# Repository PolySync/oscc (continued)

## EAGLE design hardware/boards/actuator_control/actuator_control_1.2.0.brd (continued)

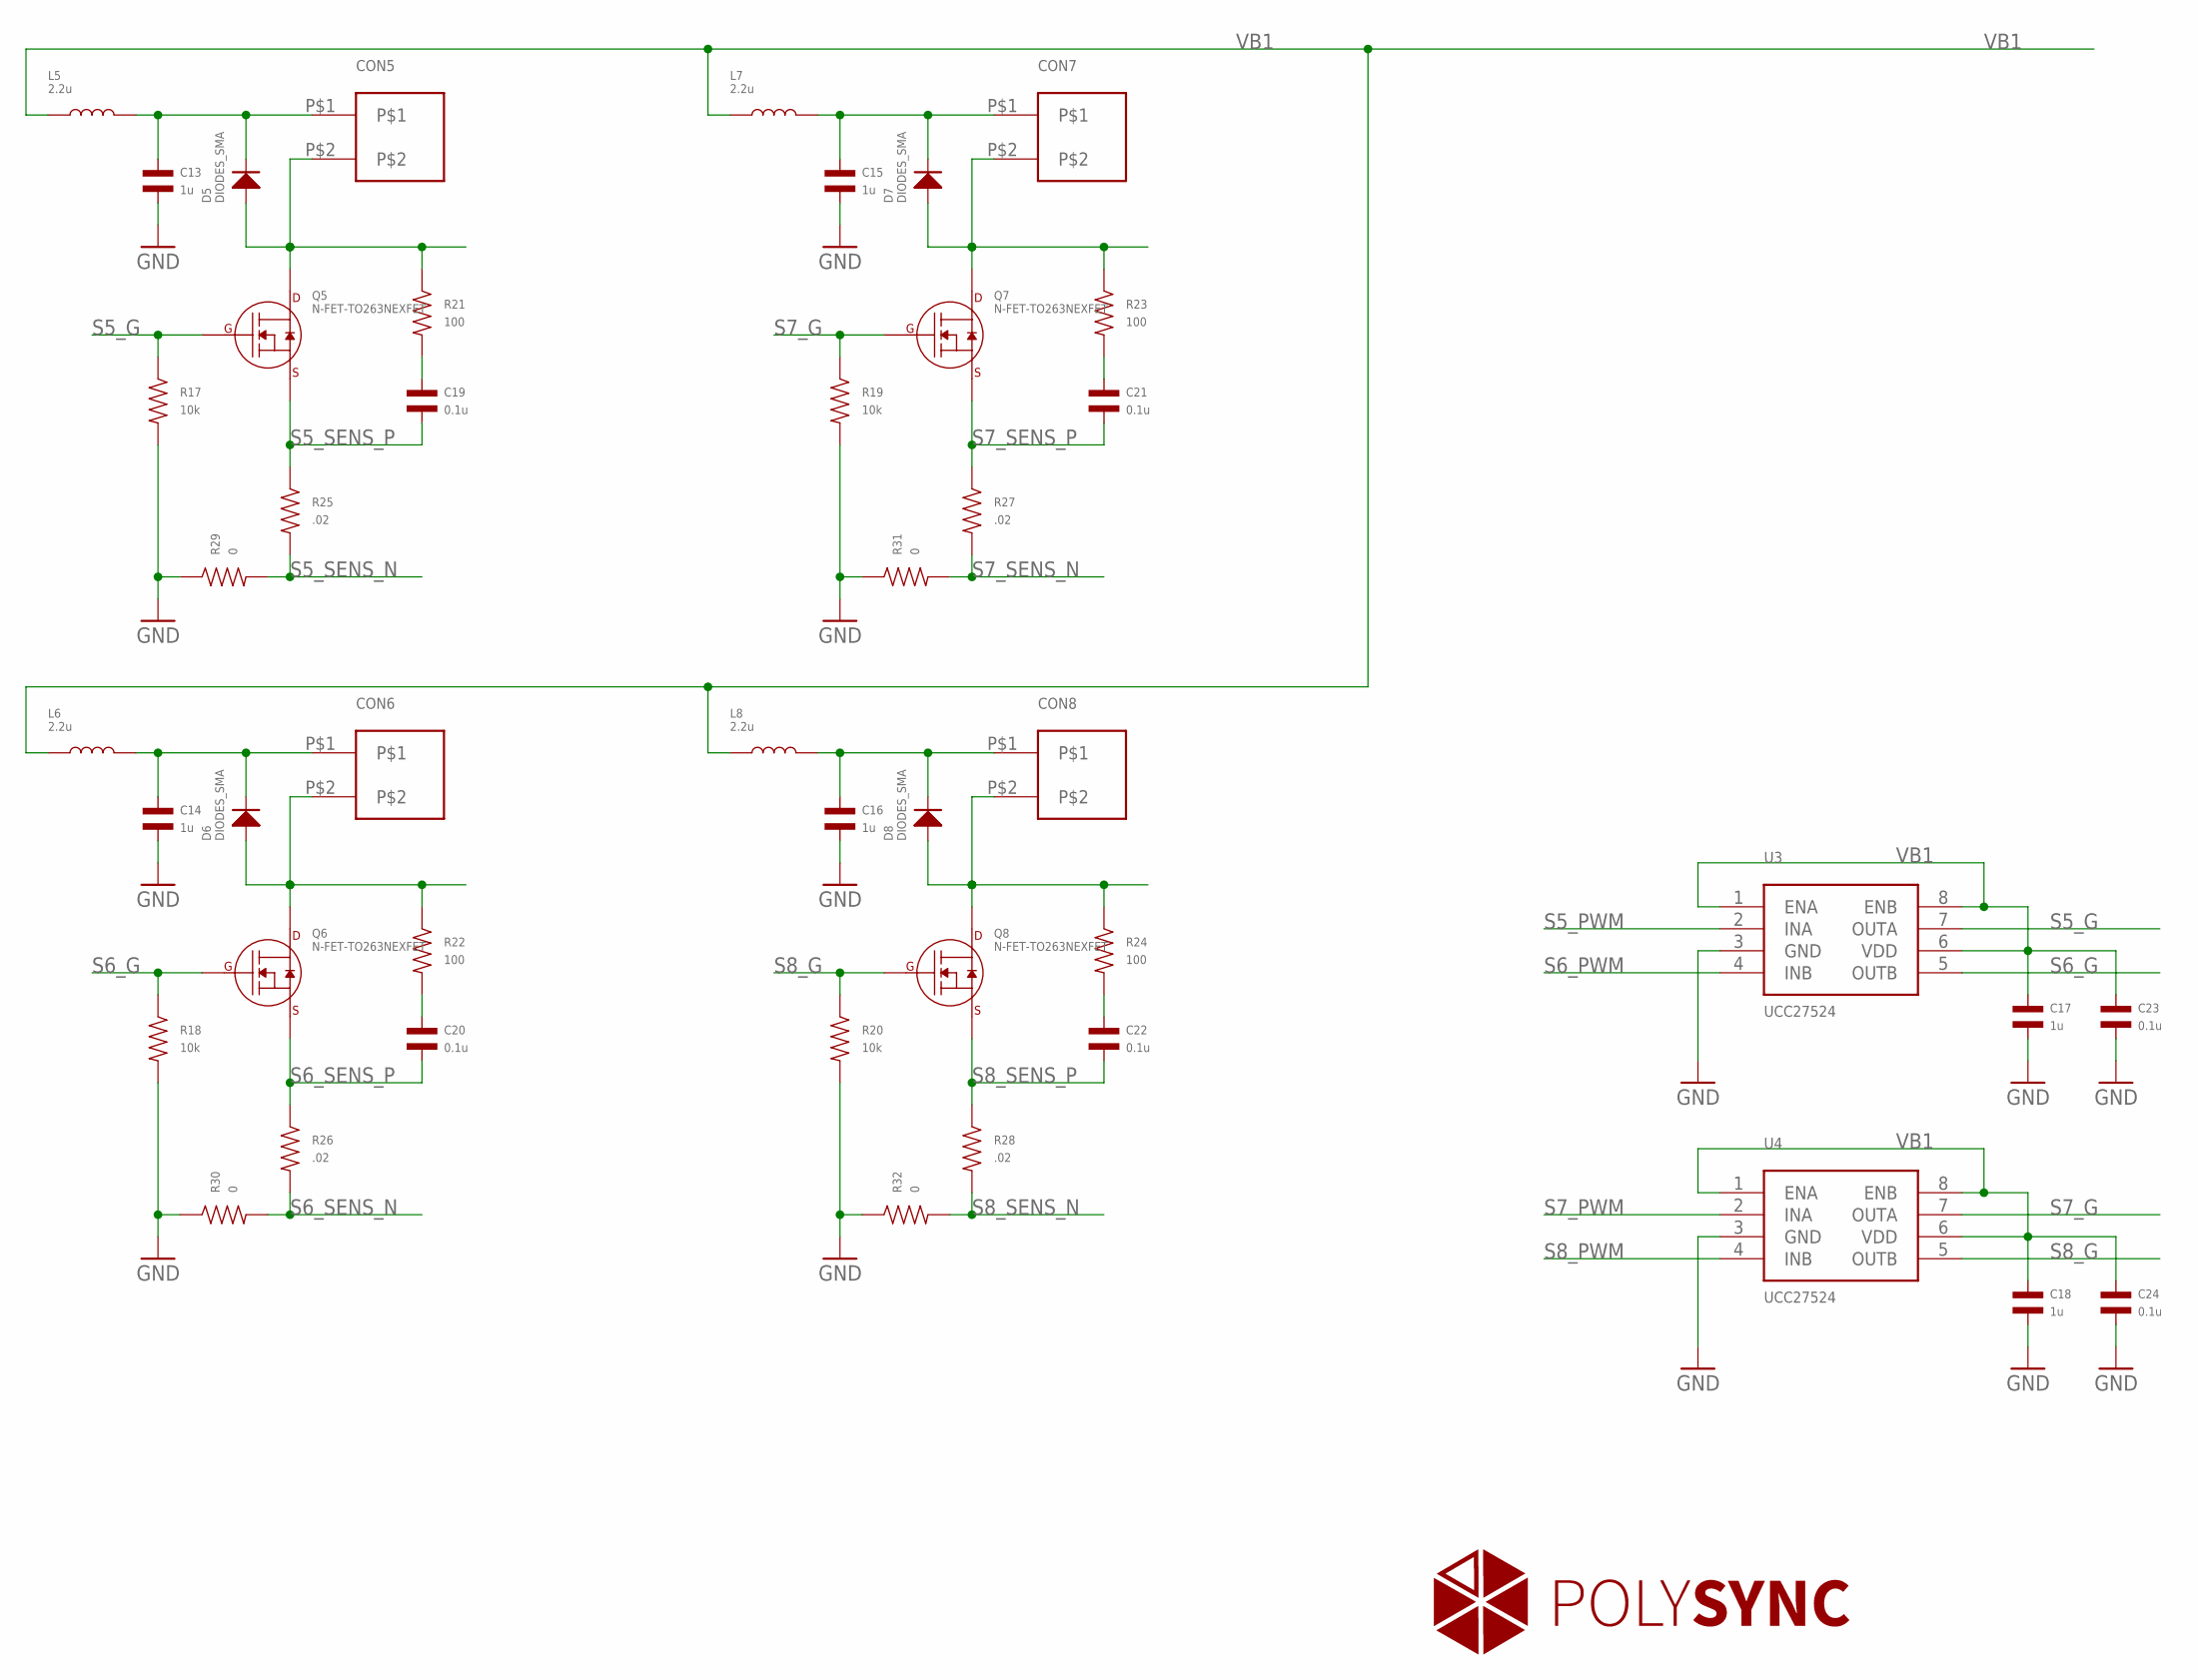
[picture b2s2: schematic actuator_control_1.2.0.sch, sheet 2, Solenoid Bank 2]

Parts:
C13, C14, C15, C16, C17, C18: 1u; C1206
C19, C20, C21, C22, C23, C24: 0.1u; C0805
CON5, CON6, CON7, CON8: CON23.5MM; PHOENIX_2_45
D5, D6, D7, D8: DIODES_SMA; SMA
L5, L6, L7, L8: 2.2u; SRP7050; PARTNO SRP7050TA-2R2M
Q5, Q6, Q7, Q8: N-FET-TO263NEXFET; SON8-DQJ
R17, R18, R19, R20: 10k; R0402
R21, R22, R23, R24: 100; R0805
R25, R26, R27, R28: .02; R1206
R29, R30, R31, R32: 0; R0805
U3, U4: UCC27524; SOIC-8

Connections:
GND: C13.P$2, C14.P$2, C15.P$2, C16.P$2, C17.P$2, C18.P$2, C23.P$2, C24.P$2, R17.P$2, R18.P$2, R19.P$2, R20.P$2, R29.P$1, R30.P$1, R31.P$1, R32.P$1, U3.3 (GND), U4.3 (GND); also elsewhere on the board
unnamed: C13.P$1, CON5.P$1, D5.CATHODE, L5.P$2
unnamed: CON5.P$2, D5.ANODE, Q5.P$5 (DRAIN), Q5.P$6 (DRAIN), Q5.P$7 (DRAIN), Q5.P$8 (DRAIN), Q5.P$9 (DRAIN), R21.P$1
unnamed: C19.P$1, R21.P$2
unnamed: C14.P$1, CON6.P$1, D6.CATHODE, L6.P$2
unnamed: CON6.P$2, D6.ANODE, Q6.P$5 (DRAIN), Q6.P$6 (DRAIN), Q6.P$7 (DRAIN), Q6.P$8 (DRAIN), Q6.P$9 (DRAIN), R22.P$1
unnamed: C20.P$1, R22.P$2
unnamed: C15.P$1, CON7.P$1, D7.CATHODE, L7.P$2
unnamed: CON7.P$2, D7.ANODE, Q7.P$5 (DRAIN), Q7.P$6 (DRAIN), Q7.P$7 (DRAIN), Q7.P$8 (DRAIN), Q7.P$9 (DRAIN), R23.P$1
unnamed: C21.P$1, R23.P$2
unnamed: C16.P$1, CON8.P$1, D8.CATHODE, L8.P$2
unnamed: CON8.P$2, D8.ANODE, Q8.P$5 (DRAIN), Q8.P$6 (DRAIN), Q8.P$7 (DRAIN), Q8.P$8 (DRAIN), Q8.P$9 (DRAIN), R24.P$1
unnamed: C22.P$1, R24.P$2
S5_G: Q5.P$4 (GATE), R17.P$1, U3.7 (OUTA)
S5_PWM: U3.2 (INA); also elsewhere on the board
S5_SENS_N: R25.P$2, R29.P$2; also elsewhere on the board
S5_SENS_P: C19.P$2, Q5.P$1 (SOURCE), Q5.P$2 (SOURCE), Q5.P$3 (SOURCE), R25.P$1; also elsewhere on the board
S6_G: Q6.P$4 (GATE), R18.P$1, U3.5 (OUTB)
S6_PWM: U3.4 (INB); also elsewhere on the board
S6_SENS_N: R26.P$2, R30.P$2; also elsewhere on the board
S6_SENS_P: C20.P$2, Q6.P$1 (SOURCE), Q6.P$2 (SOURCE), Q6.P$3 (SOURCE), R26.P$1; also elsewhere on the board
S7_G: Q7.P$4 (GATE), R19.P$1, U4.7 (OUTA)
S7_PWM: U4.2 (INA); also elsewhere on the board
S7_SENS_N: R27.P$2, R31.P$2; also elsewhere on the board
S7_SENS_P: C21.P$2, Q7.P$1 (SOURCE), Q7.P$2 (SOURCE), Q7.P$3 (SOURCE), R27.P$1; also elsewhere on the board
S8_G: Q8.P$4 (GATE), R20.P$1, U4.5 (OUTB)
S8_PWM: U4.4 (INB); also elsewhere on the board
S8_SENS_N: R28.P$2, R32.P$2; also elsewhere on the board
S8_SENS_P: C22.P$2, Q8.P$1 (SOURCE), Q8.P$2 (SOURCE), Q8.P$3 (SOURCE), R28.P$1; also elsewhere on the board
VB1: C17.P$1, C18.P$1, C23.P$1, C24.P$1, L5.P$1, L6.P$1, L7.P$1, L8.P$1, U3.1 (ENA), U3.6 (VDD), U3.8 (ENB), U4.1 (ENA), U4.6 (VDD), U4.8 (ENB); also elsewhere on the board

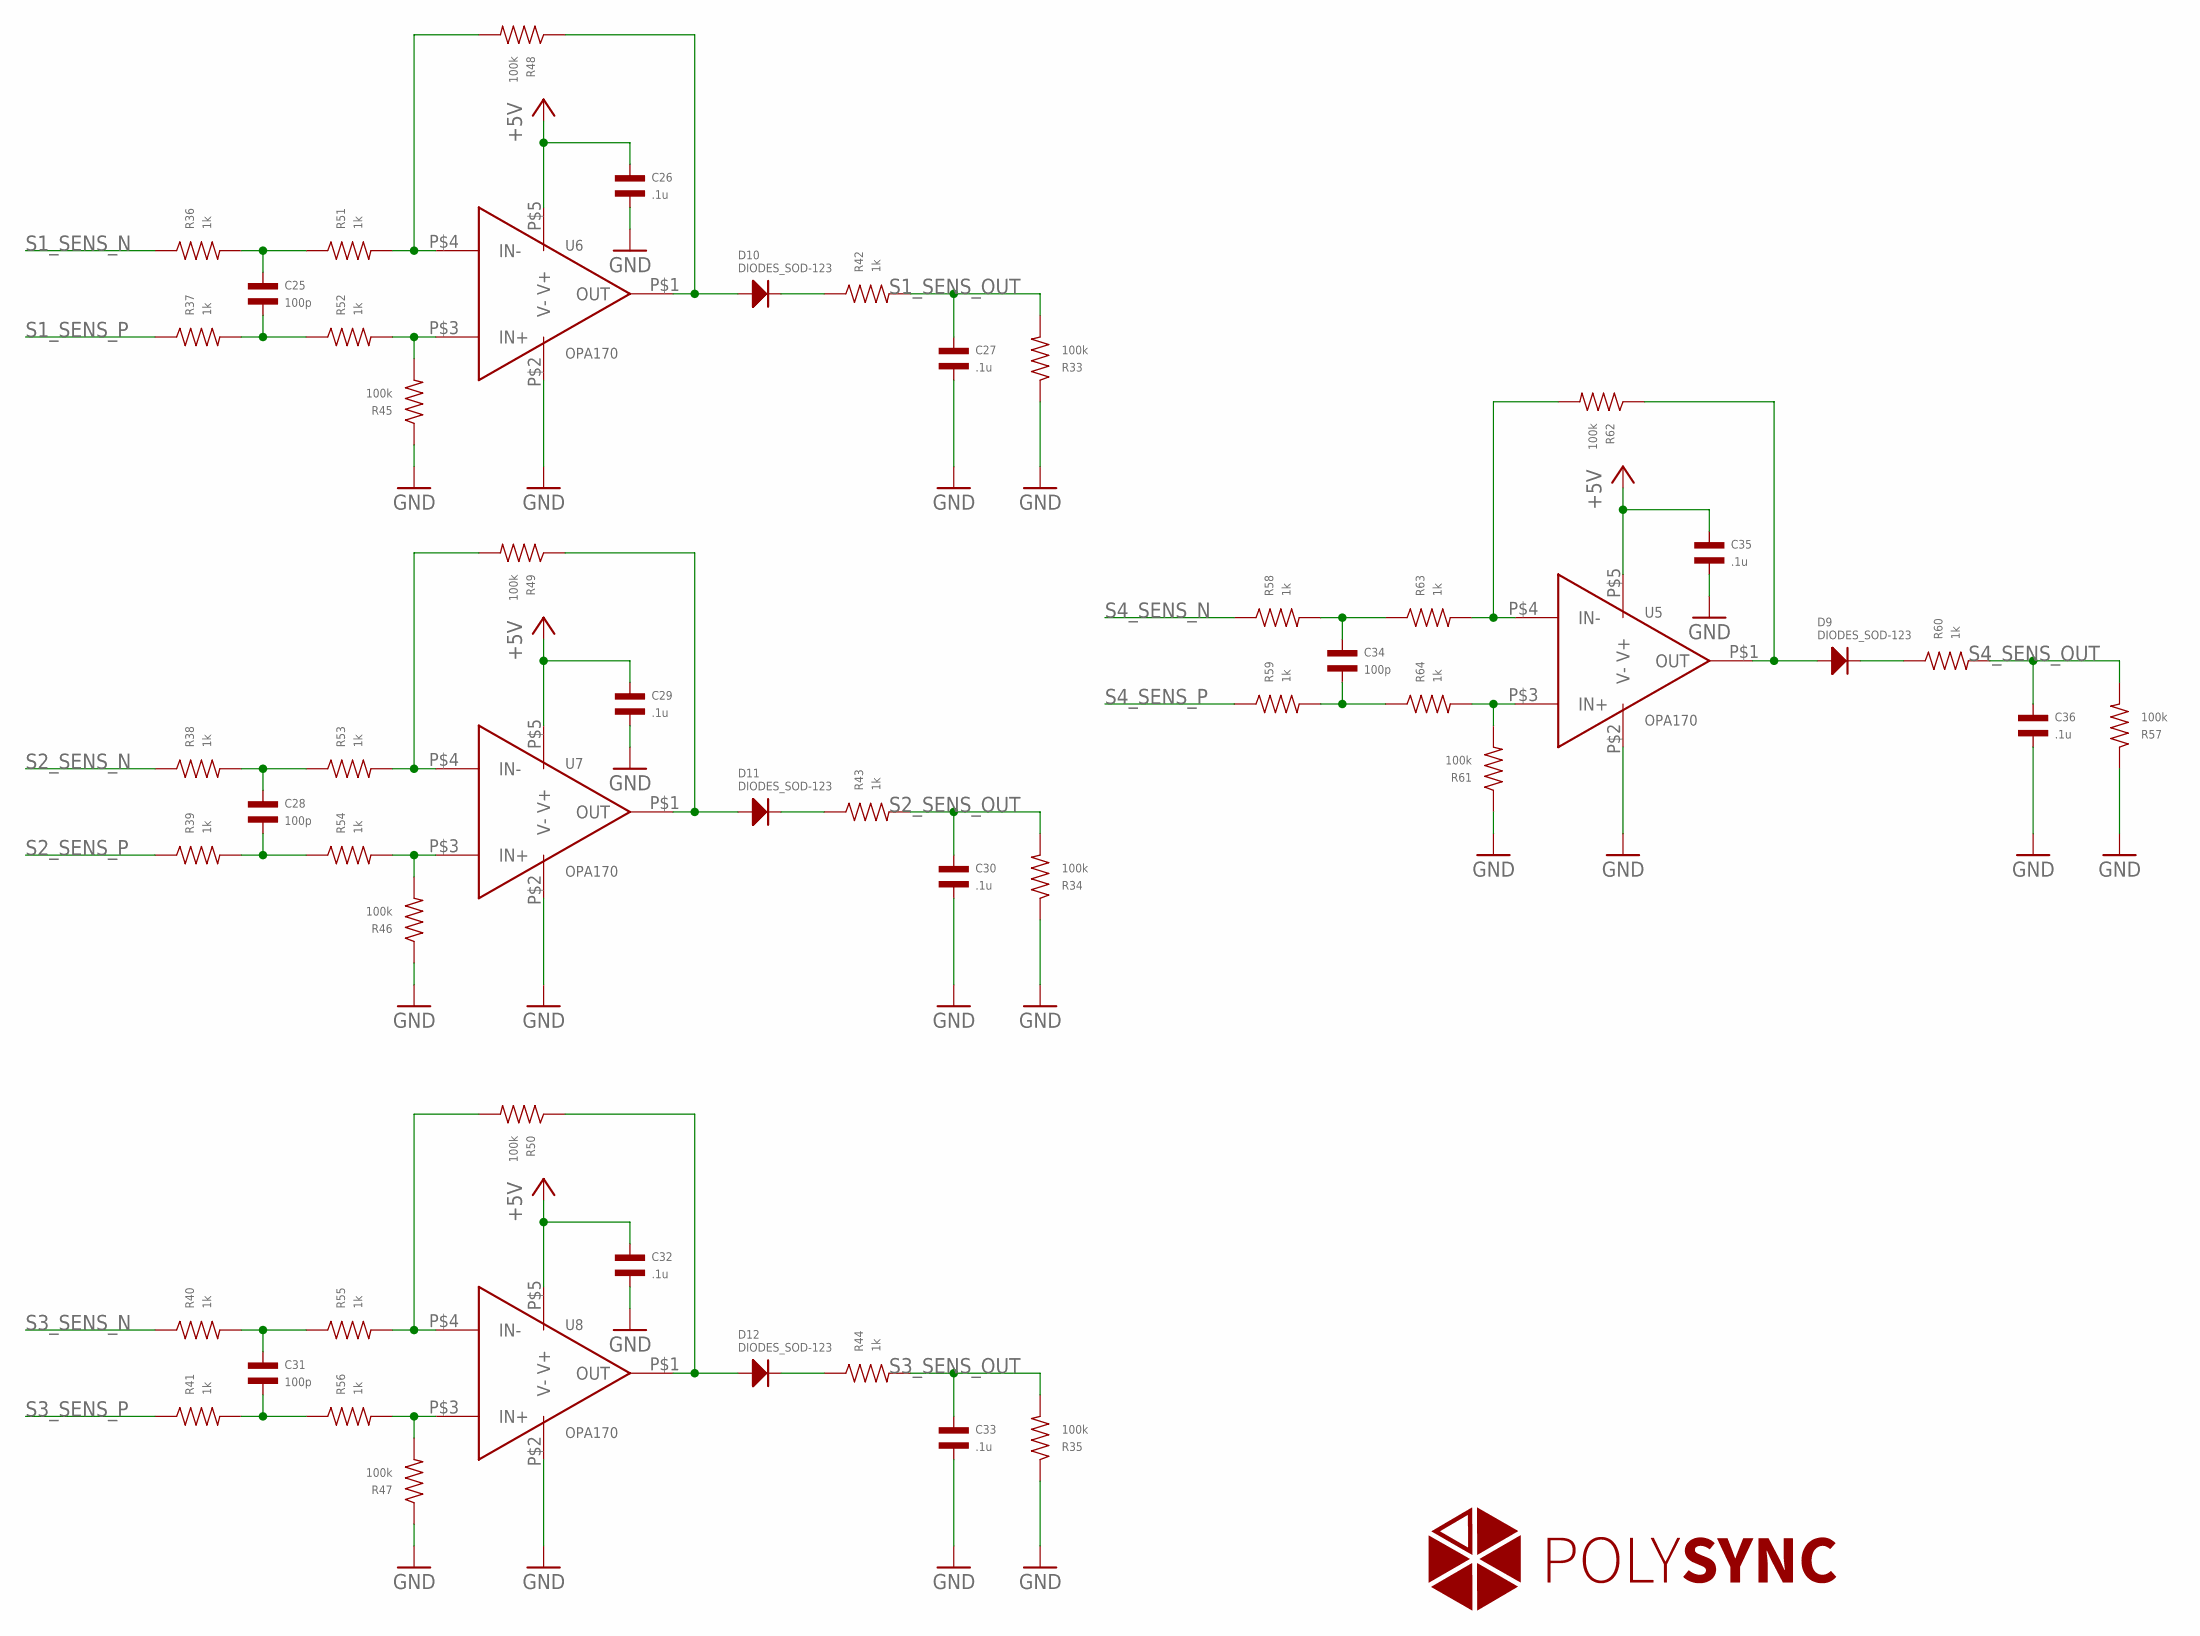
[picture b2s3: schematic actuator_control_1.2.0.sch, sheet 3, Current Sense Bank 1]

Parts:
C25, C28, C31, C34: 100p; C0402
C26, C27, C29, C30, C32, C33, C35, C36: .1u; C0402
D9, D10, D11, D12: DIODES_SOD-123; SOD-123
R33, R34, R35, R45, R46, R47, R48, R49, R50, R57, R61, R62: 100k; R0402
R36, R37, R38, R39, R40, R41, R42, R43, R44, R51, R52, R53, R54, R55, R56, R58, R59, R60, R63, R64: 1k; R0402
U5, U6, U7, U8: OPA170; SOT-23-5

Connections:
+5V: C26.P$1, C29.P$1, C32.P$1, C35.P$1, U5.P$5 (V+), U6.P$5 (V+), U7.P$5 (V+), U8.P$5 (V+); also elsewhere on the board
GND: C26.P$2, C27.P$2, C29.P$2, C30.P$2, C32.P$2, C33.P$2, C35.P$2, C36.P$2, R33.P$1, R34.P$1, R35.P$1, R45.P$1, R46.P$1, R47.P$1, R57.P$1, R61.P$1, U5.P$2 (V-), U6.P$2 (V-), U7.P$2 (V-), U8.P$2 (V-); also elsewhere on the board
unnamed: R48.P$2, R51.P$2, U6.P$4 (IN-)
unnamed: R45.P$2, R52.P$2, U6.P$3 (IN+)
unnamed: C25.P$2, R37.P$2, R52.P$1
unnamed: C25.P$1, R36.P$2, R51.P$1
unnamed: D10.ANODE, R48.P$1, U6.P$1 (OUT)
unnamed: D10.CATHODE, R42.P$1
unnamed: R49.P$2, R53.P$2, U7.P$4 (IN-)
unnamed: R46.P$2, R54.P$2, U7.P$3 (IN+)
unnamed: C28.P$2, R39.P$2, R54.P$1
unnamed: C28.P$1, R38.P$2, R53.P$1
unnamed: D11.ANODE, R49.P$1, U7.P$1 (OUT)
unnamed: D11.CATHODE, R43.P$1
unnamed: R50.P$2, R55.P$2, U8.P$4 (IN-)
unnamed: R47.P$2, R56.P$2, U8.P$3 (IN+)
unnamed: C31.P$2, R41.P$2, R56.P$1
unnamed: C31.P$1, R40.P$2, R55.P$1
unnamed: D12.ANODE, R50.P$1, U8.P$1 (OUT)
unnamed: D12.CATHODE, R44.P$1
unnamed: R62.P$2, R63.P$2, U5.P$4 (IN-)
unnamed: R61.P$2, R64.P$2, U5.P$3 (IN+)
unnamed: C34.P$2, R59.P$2, R64.P$1
unnamed: C34.P$1, R58.P$2, R63.P$1
unnamed: D9.ANODE, R62.P$1, U5.P$1 (OUT)
unnamed: D9.CATHODE, R60.P$1
S1_SENS_N: R36.P$1; also elsewhere on the board
S1_SENS_OUT: C27.P$1, R33.P$2, R42.P$2; also elsewhere on the board
S1_SENS_P: R37.P$1; also elsewhere on the board
S2_SENS_N: R38.P$1; also elsewhere on the board
S2_SENS_OUT: C30.P$1, R34.P$2, R43.P$2; also elsewhere on the board
S2_SENS_P: R39.P$1; also elsewhere on the board
S3_SENS_N: R40.P$1; also elsewhere on the board
S3_SENS_OUT: C33.P$1, R35.P$2, R44.P$2; also elsewhere on the board
S3_SENS_P: R41.P$1; also elsewhere on the board
S4_SENS_N: R58.P$1; also elsewhere on the board
S4_SENS_OUT: C36.P$1, R57.P$2, R60.P$2; also elsewhere on the board
S4_SENS_P: R59.P$1; also elsewhere on the board

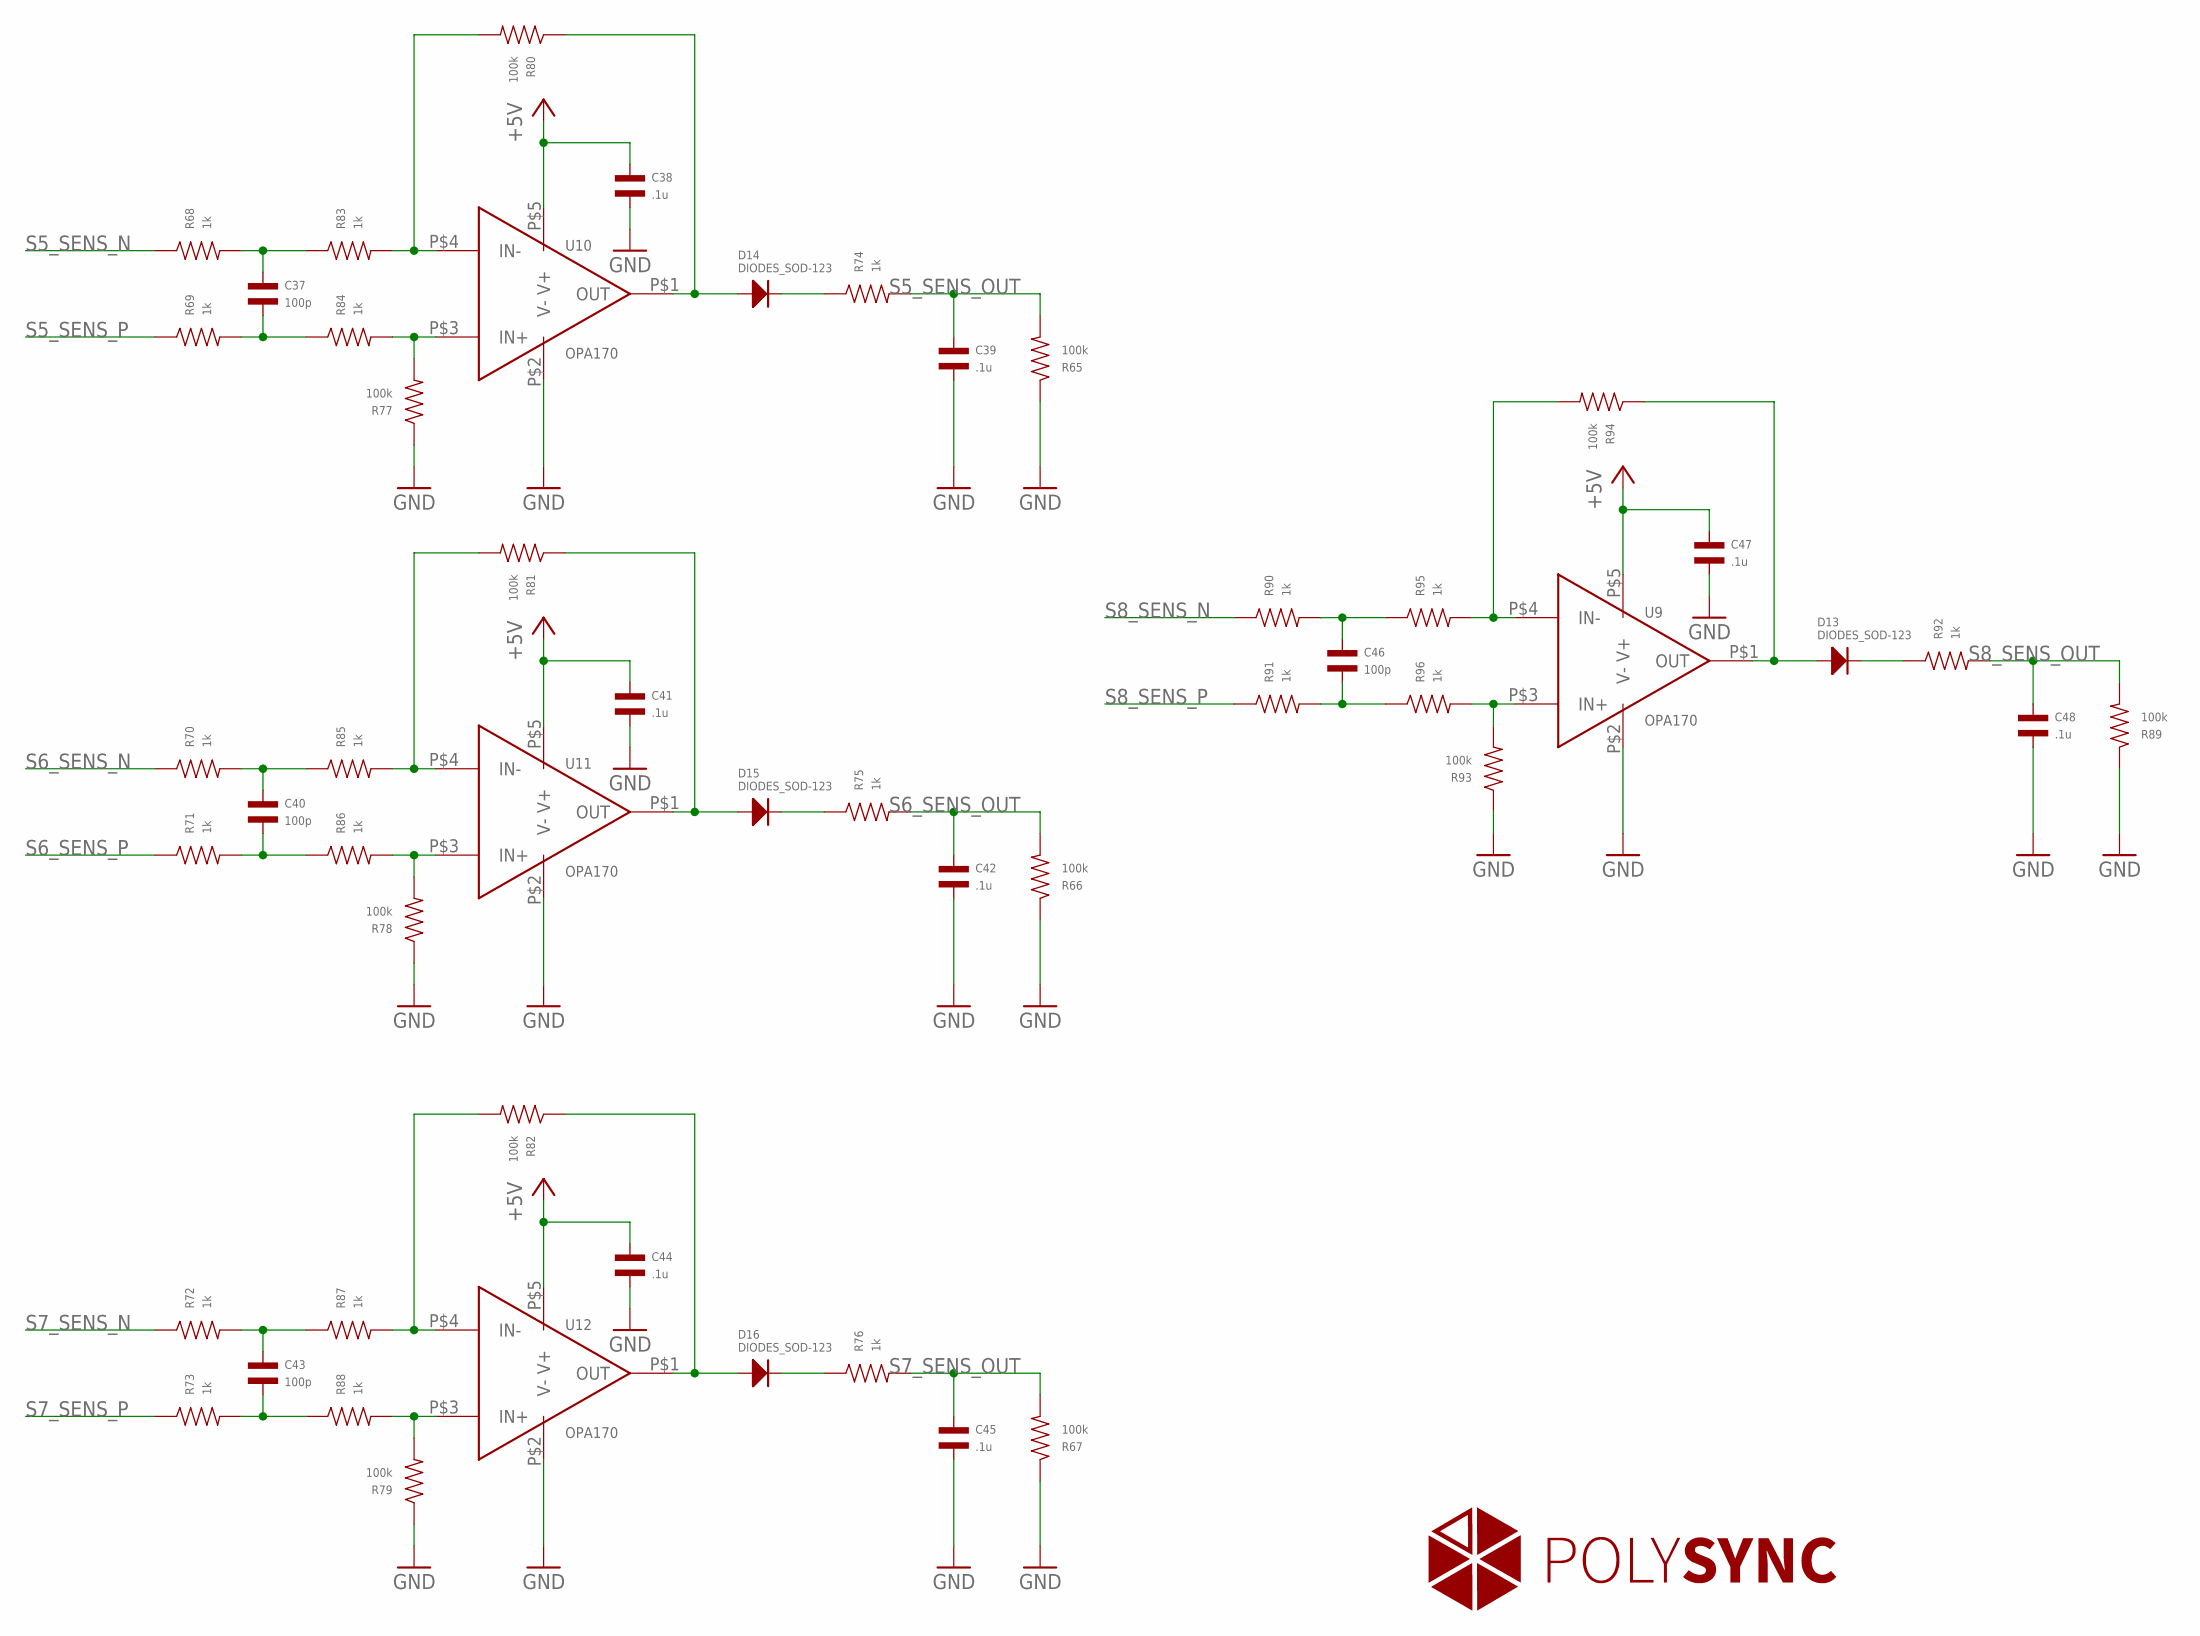
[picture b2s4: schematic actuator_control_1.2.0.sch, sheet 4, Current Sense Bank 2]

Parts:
C37, C40, C43, C46: 100p; C0402
C38, C39, C41, C42, C44, C45, C47, C48: .1u; C0402
D13, D14, D15, D16: DIODES_SOD-123; SOD-123
R65, R66, R67, R77, R78, R79, R80, R81, R82, R89, R93, R94: 100k; R0402
R68, R69, R70, R71, R72, R73, R74, R75, R76, R83, R84, R85, R86, R87, R88, R90, R91, R92, R95, R96: 1k; R0402
U9, U10, U11, U12: OPA170; SOT-23-5

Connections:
+5V: C38.P$1, C41.P$1, C44.P$1, C47.P$1, U9.P$5 (V+), U10.P$5 (V+), U11.P$5 (V+), U12.P$5 (V+); also elsewhere on the board
GND: C38.P$2, C39.P$2, C41.P$2, C42.P$2, C44.P$2, C45.P$2, C47.P$2, C48.P$2, R65.P$1, R66.P$1, R67.P$1, R77.P$1, R78.P$1, R79.P$1, R89.P$1, R93.P$1, U9.P$2 (V-), U10.P$2 (V-), U11.P$2 (V-), U12.P$2 (V-); also elsewhere on the board
unnamed: R80.P$2, R83.P$2, U10.P$4 (IN-)
unnamed: R77.P$2, R84.P$2, U10.P$3 (IN+)
unnamed: C37.P$2, R69.P$2, R84.P$1
unnamed: C37.P$1, R68.P$2, R83.P$1
unnamed: D14.ANODE, R80.P$1, U10.P$1 (OUT)
unnamed: D14.CATHODE, R74.P$1
unnamed: R81.P$2, R85.P$2, U11.P$4 (IN-)
unnamed: R78.P$2, R86.P$2, U11.P$3 (IN+)
unnamed: C40.P$2, R71.P$2, R86.P$1
unnamed: C40.P$1, R70.P$2, R85.P$1
unnamed: D15.ANODE, R81.P$1, U11.P$1 (OUT)
unnamed: D15.CATHODE, R75.P$1
unnamed: R82.P$2, R87.P$2, U12.P$4 (IN-)
unnamed: R79.P$2, R88.P$2, U12.P$3 (IN+)
unnamed: C43.P$2, R73.P$2, R88.P$1
unnamed: C43.P$1, R72.P$2, R87.P$1
unnamed: D16.ANODE, R82.P$1, U12.P$1 (OUT)
unnamed: D16.CATHODE, R76.P$1
unnamed: R94.P$2, R95.P$2, U9.P$4 (IN-)
unnamed: R93.P$2, R96.P$2, U9.P$3 (IN+)
unnamed: C46.P$2, R91.P$2, R96.P$1
unnamed: C46.P$1, R90.P$2, R95.P$1
unnamed: D13.ANODE, R94.P$1, U9.P$1 (OUT)
unnamed: D13.CATHODE, R92.P$1
S5_SENS_N: R68.P$1; also elsewhere on the board
S5_SENS_OUT: C39.P$1, R65.P$2, R74.P$2; also elsewhere on the board
S5_SENS_P: R69.P$1; also elsewhere on the board
S6_SENS_N: R70.P$1; also elsewhere on the board
S6_SENS_OUT: C42.P$1, R66.P$2, R75.P$2; also elsewhere on the board
S6_SENS_P: R71.P$1; also elsewhere on the board
S7_SENS_N: R72.P$1; also elsewhere on the board
S7_SENS_OUT: C45.P$1, R67.P$2, R76.P$2; also elsewhere on the board
S7_SENS_P: R73.P$1; also elsewhere on the board
S8_SENS_N: R90.P$1; also elsewhere on the board
S8_SENS_OUT: C48.P$1, R89.P$2, R92.P$2; also elsewhere on the board
S8_SENS_P: R91.P$1; also elsewhere on the board

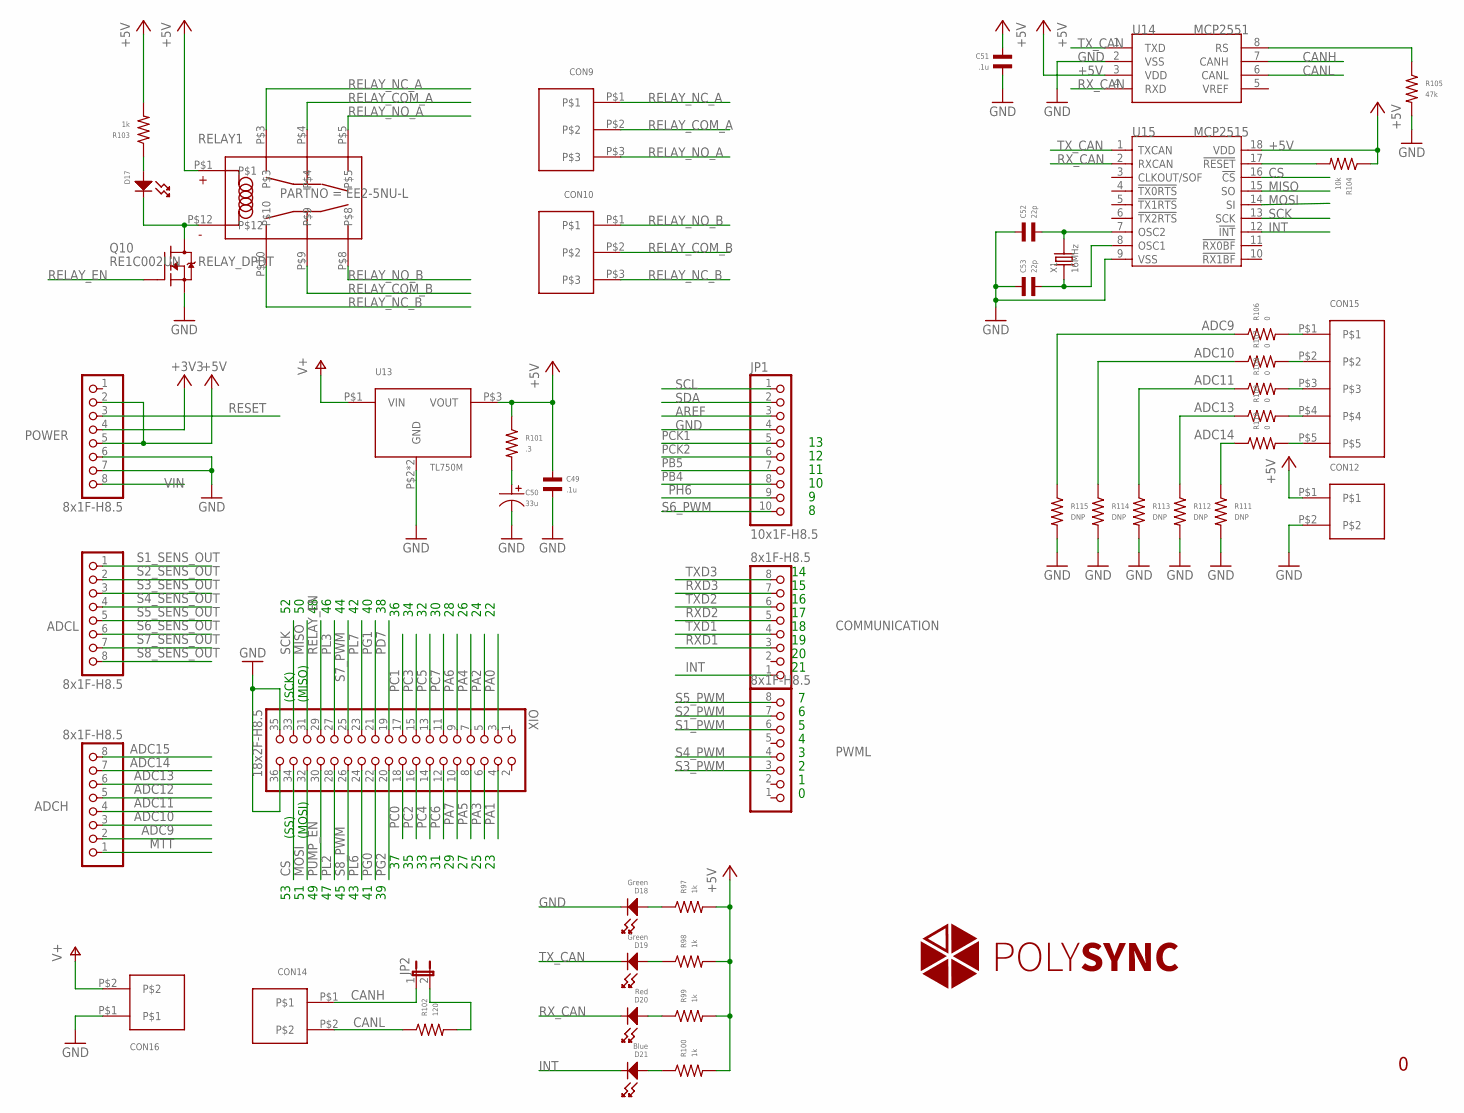
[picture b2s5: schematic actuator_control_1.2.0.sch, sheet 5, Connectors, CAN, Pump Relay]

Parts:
ADCH: 8x1F-H8.5; 1X08
ADCL: 8x1F-H8.5; 1X08
C49, C51: .1u; C0402
C50: 33u; CP1206
C52, C53: 22p; C0402
COMMUNICATION: 8x1F-H8.5; 1X08
CON9, CON10: CON3; PHOENIX_3_45
CON12, CON14: CON23.5MM; PHOENIX_2_45
CON15: CON5; PHOENIX_5_45
CON16: CON23.5MM; PHOENIX_2_45; PARTNO 1773976
D17: LED_SINGLE-0603; LED0603
D18, D19: Green; LED0603
D20: Red; LED0603
D21: Blue; LED0603
JP1: 10x1F-H8.5; 1X10
JP2: JP1E; JP1
POWER: 8x1F-H8.5; 1X08
PWML: 8x1F-H8.5; 1X08
Q10: RE1C002UN; EMT3F
R97, R98, R99, R100, R103: 1k; R0402
R101: .3; R0402
R102: 120; R0402
R104: 10k; R0402
R105: 47k; R0402
R106, R107, R108, R109, R110: 0; R0402
R111, R112, R113, R114, R115: DNP; R0402
RELAY1: RELAY_DPDT; KEMET_EE2; PARTNO EE2-5NU-L
U13: TL750M; TO-263
U14: MCP2551; SOIC8-6.0
U15: MCP2515; SOIC18
X1: 16MHz; HC49UP
XIO: 18x2F-H8.5; 2X18

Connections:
+3V3: POWER.4
+5V: C49.P$1, C51.P$1, CON12.P$1, POWER.2, POWER.5, R97.P$2, R98.P$2, R99.P$2, R100.P$2, R101.P$1, R103.P$2, R104.P$1, RELAY1.P$1, U13.P$3 (VOUT), U14.3 (VDD), U15.18 (VDD); also elsewhere on the board
ADC9: ADCH.2, R106.P$1, R115.P$1
ADC10: ADCH.3, R107.P$1, R114.P$1
ADC11: ADCH.4, R108.P$1, R113.P$1
ADC12: ADCH.5; also elsewhere on the board
ADC13: ADCH.6, R109.P$1, R112.P$1
ADC14: ADCH.7, R110.P$1, R111.P$1
ADC15: ADCH.8
AREF: JP1.3
CANH: CON14.P$1, JP2.1, U14.7 (CANH)
CANL: CON14.P$2, R102.P$1, U14.6 (CANL)
CS: U15.16 (!CS), XIO.34
GND: C49.P$2, C50.P$2, C51.P$2, C52.P$1, C53.P$1, CON12.P$2, CON16.P$1, D18.CATHODE, JP1.4, POWER.6, POWER.7, Q10.P$2 (S), R105.P$2, R111.P$2, R112.P$2, R113.P$2, R114.P$2, R115.P$2, U13.P$2 (GND), U13.P$4 (GND), U14.2 (VSS), U15.9 (VSS), XIO.35, XIO.36; also elsewhere on the board
INT: COMMUNICATION.1, D21.CATHODE, U15.12 (!INT)
MISO: U15.15 (SO), XIO.31
MOSI: U15.14 (SI), XIO.32
MTT: ADCH.1; also elsewhere on the board
unnamed: CON15.P$1, R106.P$2
unnamed: CON15.P$2, R107.P$2
unnamed: CON15.P$3, R108.P$2
unnamed: C52.P$2, U15.7 (OSC2), X1.2
unnamed: C53.P$2, U15.8 (OSC1), X1.1
unnamed: D17.CATHODE, Q10.P$3 (D), RELAY1.P$12
unnamed: D18.ANODE, R97.P$1
unnamed: D19.ANODE, R98.P$1
unnamed: D20.ANODE, R99.P$1
unnamed: D21.ANODE, R100.P$1
unnamed: R105.P$1, U14.8 (RS)
unnamed: D17.ANODE, R103.P$1
unnamed: CON15.P$4, R109.P$2
unnamed: CON15.P$5, R110.P$2
unnamed: C50.P$1, R101.P$2
unnamed: JP2.2, R102.P$2
PA0: XIO.3
PA1: XIO.4
PA2: XIO.5
PA3: XIO.6
PA4: XIO.7
PA5: XIO.8
PA6: XIO.9
PA7: XIO.10
PB4: JP1.8
PB5: JP1.7
PC0: XIO.18
PC1: XIO.17
PC2: XIO.16
PC3: XIO.15
PC4: XIO.14
PC5: XIO.13
PC6: XIO.12
PC7: XIO.11
PCK1: JP1.5; also elsewhere on the board
PCK2: JP1.6; also elsewhere on the board
PD7: XIO.19
PG0: XIO.22
PG1: XIO.21
PG2: XIO.20
PH6: JP1.9
PL2: XIO.28
PL3: XIO.27
PL6: XIO.24
PL7: XIO.23
PUMP_EN: XIO.30; also elsewhere on the board
RELAY_COM_A: CON9.P$2, RELAY1.P$4
RELAY_COM_B: CON10.P$2, RELAY1.P$9
RELAY_EN: Q10.P$1 (G), XIO.29
RELAY_NC_A: CON9.P$1, RELAY1.P$3
RELAY_NC_B: CON10.P$3, RELAY1.P$10
RELAY_NO_A: CON9.P$3, RELAY1.P$5
RELAY_NO_B: CON10.P$1, RELAY1.P$8
RESET: POWER.3
RST_N2: R104.P$2, U15.17 (!RESET)
RXD1: COMMUNICATION.3
RXD2: COMMUNICATION.5
RXD3: COMMUNICATION.7
RX_CAN: D20.CATHODE, U14.4 (RXD), U15.2 (RXCAN)
S1_PWM: PWML.6; also elsewhere on the board
S1_SENS_OUT: ADCL.1; also elsewhere on the board
S2_PWM: PWML.7; also elsewhere on the board
S2_SENS_OUT: ADCL.2; also elsewhere on the board
S3_PWM: PWML.3; also elsewhere on the board
S3_SENS_OUT: ADCL.3; also elsewhere on the board
S4_PWM: PWML.4; also elsewhere on the board
S4_SENS_OUT: ADCL.4; also elsewhere on the board
S5_PWM: PWML.8; also elsewhere on the board
S5_SENS_OUT: ADCL.5; also elsewhere on the board
S6_PWM: JP1.10; also elsewhere on the board
S6_SENS_OUT: ADCL.6; also elsewhere on the board
S7_PWM: XIO.25; also elsewhere on the board
S7_SENS_OUT: ADCL.7; also elsewhere on the board
S8_PWM: XIO.26; also elsewhere on the board
S8_SENS_OUT: ADCL.8; also elsewhere on the board
SCK: U15.13 (SCK), XIO.33
SCL: JP1.1
SDA: JP1.2
TXD1: COMMUNICATION.4
TXD2: COMMUNICATION.6
TXD3: COMMUNICATION.8
TX_CAN: D19.CATHODE, U14.1 (TXD), U15.1 (TXCAN)
V+: CON16.P$2, U13.P$1 (VIN); also elsewhere on the board
VIN: POWER.8

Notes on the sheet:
(SS)
(MOSI)
(SCK)
(MISO)
